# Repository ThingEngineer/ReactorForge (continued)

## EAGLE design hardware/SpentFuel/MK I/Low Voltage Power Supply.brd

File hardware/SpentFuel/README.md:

ReactorForge - SpentFuel
============

SpentFuel is where the older prototypes that have provided a foundation for other models, learning experice and or headaches are stored. Proceed with caution!

Schematic and board designs are in CadSoft EAGLE PCB Design Software.

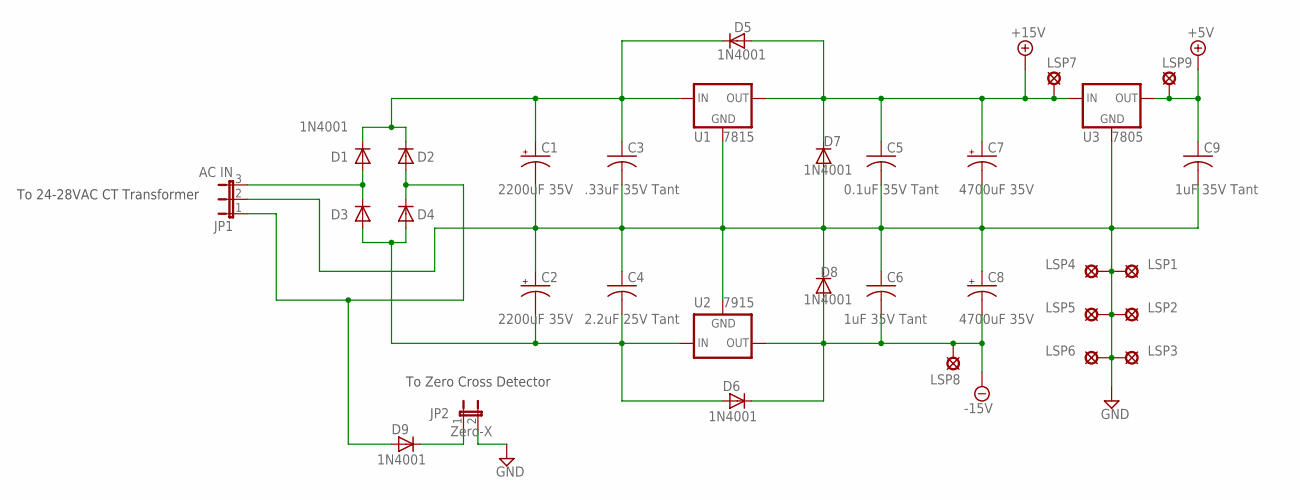
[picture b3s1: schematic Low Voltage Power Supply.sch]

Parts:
C1, C2: 2200uF 35V; E7,5-18
C3: .33uF 35V Tant; C1206
C4: 2.2uF 25V Tant; C1206
C5: 0.1uF 35V Tant; C1206
C6, C9: 1uF 35V Tant; C1206
C7, C8: 4700uF 35V; E7,5-18
D1, D2, D3, D4, D5, D6, D7, D8, D9: 1N4001; DIODE.4-AXIAL
JP1: AC IN; JP2
JP2: Zero-X; JP1
LSP1, LSP2, LSP3, LSP4, LSP5, LSP6, LSP7, LSP8, LSP9: SE14
U1: 7815; 78XXS
U2: 7915; 79XXS
U3: 7805; 78XXS

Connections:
+5V: C9.1, LSP9.MP, U3.OUT
+15V: C5.1, C7.+, D5.A, D7.C, LSP7.MP, U1.OUT, U3.IN
-15V: C6.2, C8.-, D6.C, D8.A, LSP8.MP, U2.OUT
GND: C1.-, C2.+, C3.2, C4.1, C5.2, C6.1, C7.-, C8.+, C9.2, D7.A, D8.C, JP1.2, JP2.2, LSP1.MP, LSP2.MP, LSP3.MP, LSP4.MP, LSP5.MP, LSP6.MP, U1.GND, U2.GND, U3.GND
unnamed: C1.+, C3.1, D1.C, D2.C, D5.C, U1.IN
unnamed: D2.A, D4.C, D9.A, JP1.1
unnamed: D1.A, D3.C, JP1.3
unnamed: C2.-, C4.2, D3.A, D4.A, D6.A, U2.IN
unnamed: D9.C, JP2.1

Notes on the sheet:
To Zero Cross Detector
To 24-28VAC CT Transformer

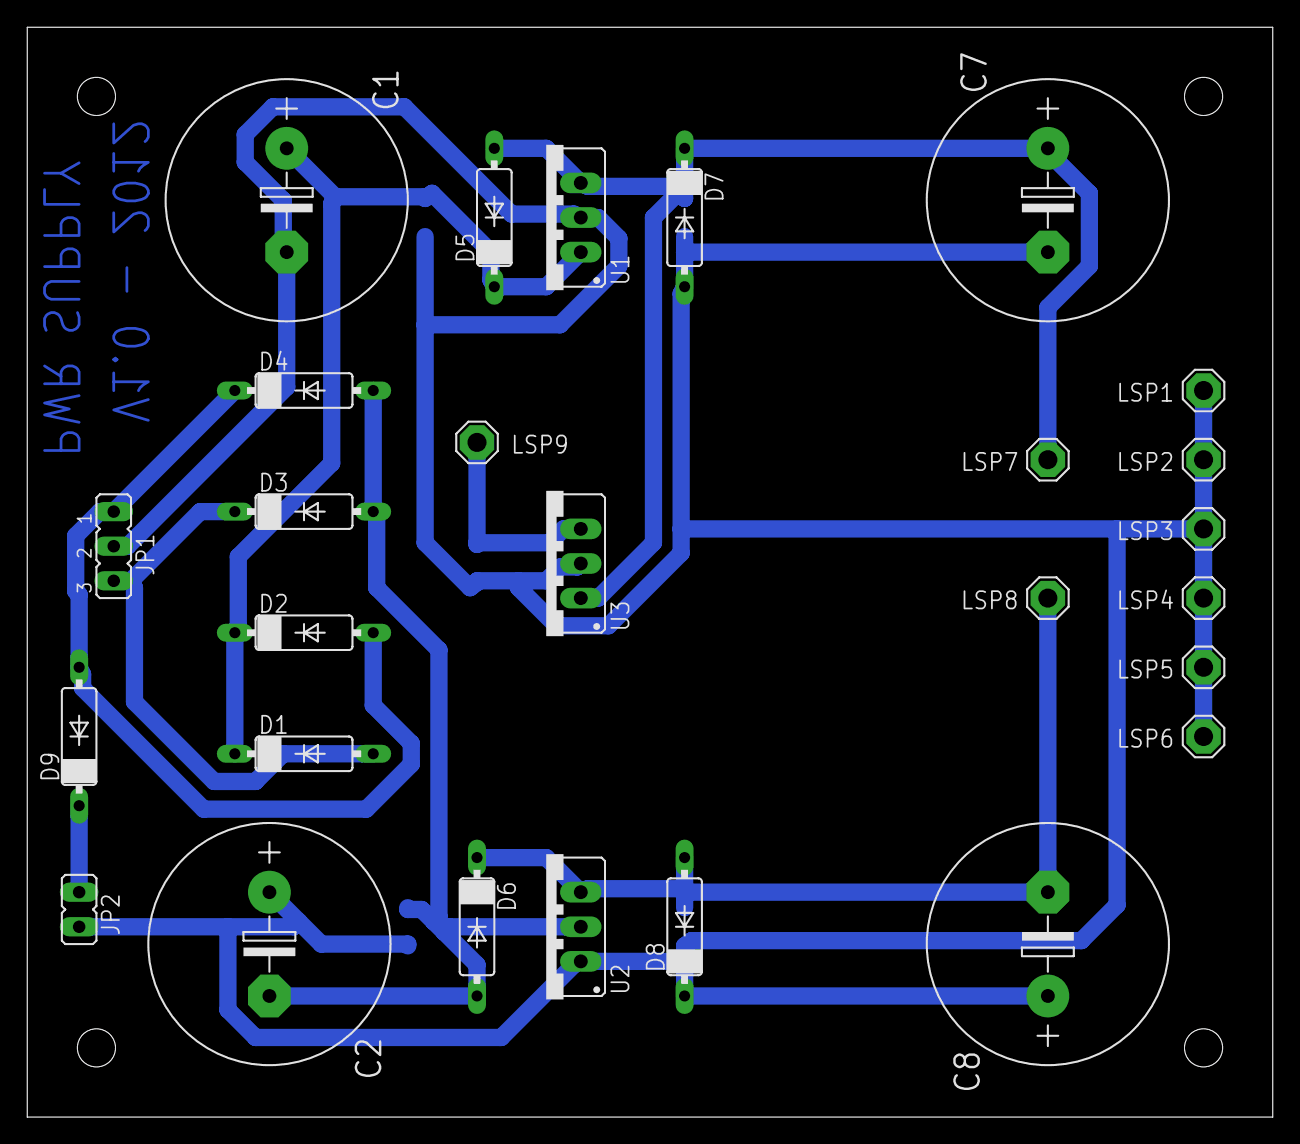
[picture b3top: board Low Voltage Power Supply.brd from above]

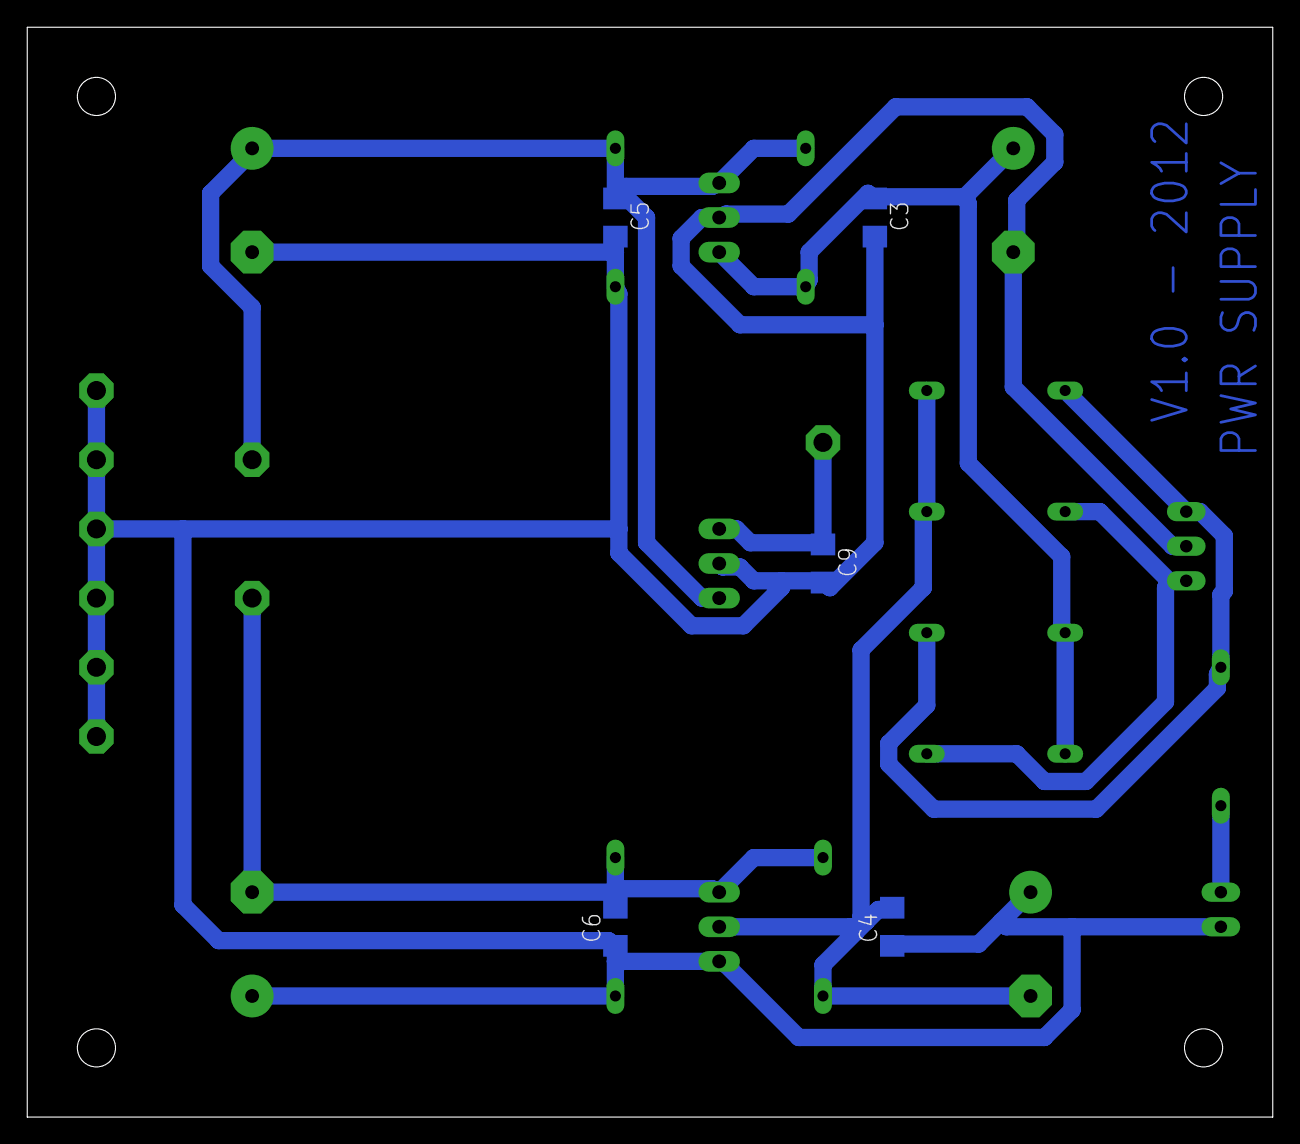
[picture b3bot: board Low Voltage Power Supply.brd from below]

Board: 2 copper layers, 91.4 x 80.0 mm, 32 parts (5 on the bottom side), 9 nets.

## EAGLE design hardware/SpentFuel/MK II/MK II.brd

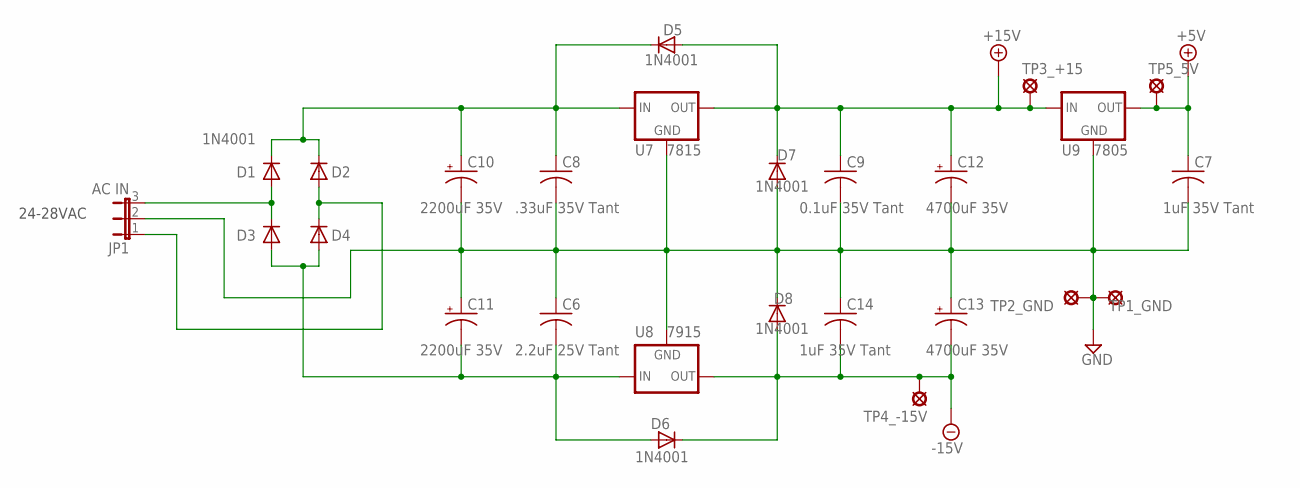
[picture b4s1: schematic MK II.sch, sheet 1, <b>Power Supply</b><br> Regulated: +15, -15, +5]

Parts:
C6: 2.2uF 25V Tant; C1206
C7, C14: 1uF 35V Tant; C1206
C8: .33uF 35V Tant; C1206
C9: 0.1uF 35V Tant; C1206
C10, C11: 2200uF 35V; E7,5-18
C12, C13: 4700uF 35V; E7,5-18
D1, D2, D3, D4, D5, D6, D7, D8: 1N4001; DIODE.4-AXIAL
JP1: AC IN; JP2
TP1_GND, TP2_GND, TP3_+15, TP4_-15V, TP5_5V: SE14
U7: 7815; 78XXS
U8: 7915; 79XXS
U9: 7805; 78XXS

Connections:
+5V: C7.1, TP5_5V.MP, U9.OUT; also elsewhere on the board
+15V: C9.1, C12.+, D5.A, D7.C, TP3_+15.MP, U7.OUT, U9.IN; also elsewhere on the board
-15V: C13.-, C14.2, D6.C, D8.A, TP4_-15V.MP, U8.OUT; also elsewhere on the board
GND: C6.1, C7.2, C8.2, C9.2, C10.-, C11.+, C12.-, C13.+, C14.1, D7.A, D8.C, JP1.2, TP1_GND.MP, TP2_GND.MP, U7.GND, U8.GND, U9.GND; also elsewhere on the board
unnamed: C8.1, C10.+, D1.C, D2.C, D5.C, U7.IN
unnamed: D2.A, D4.C, JP1.1
unnamed: D1.A, D3.C, JP1.3
unnamed: C6.2, C11.-, D3.A, D4.A, D6.A, U8.IN

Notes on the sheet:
24-28VAC

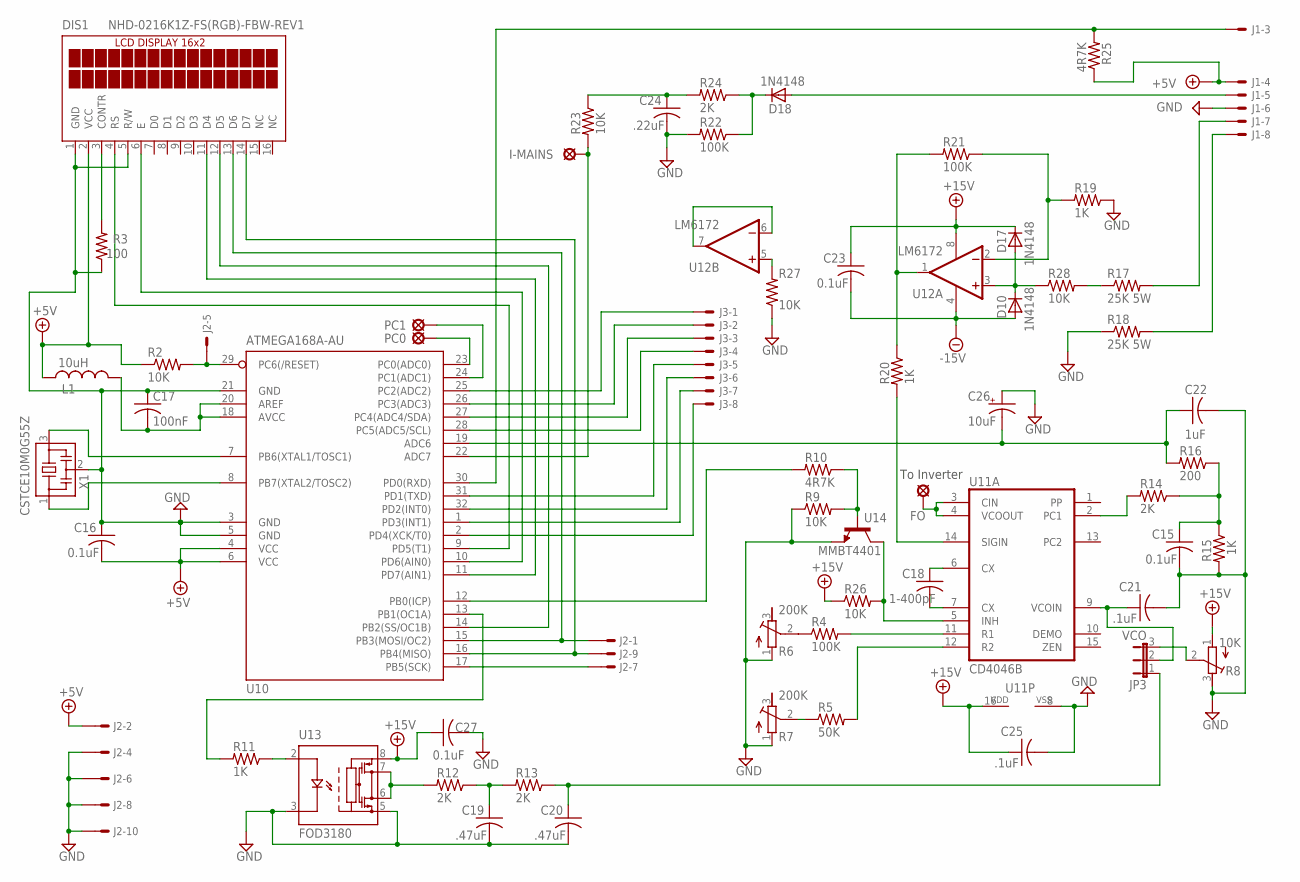
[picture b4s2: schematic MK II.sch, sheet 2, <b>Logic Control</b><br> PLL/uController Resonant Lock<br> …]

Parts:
C15, C16, C23, C27: 0.1uF; C1206
C17: 100nF; C1206
C18: 1-400pF; C1206
C19, C20: .47uF; C1206
C21, C25: .1uF; C1206
C22: 1uF; C1206
C24: .22uF; C1206
C26: 10uF; E2,5-7
D10, D17, D18: 1N4148; SOD-123
DIS1: NHD-0216K1Z-FS(RGB)-FBW-REV1; TUXGR_16X2_R2
FO: SE14
I-MAINS: SE14
J1, J3: 22-23-2081
J2: 057-010-1
JP3: VCO; JP2
L1: 10uH; L2012C
PC0, PC1: SE14
R2, R9, R23, R26, R27, R28: 10K; M1206
R3: 100; M1206
R4, R21, R22: 100K; M1206
R5: 50K; M1206
R6, R7: 200K; RTRIM4G/J
R8: 10K; RTRIM4G/J
R10, R25: 4R7K; M1206
R11, R15, R19, R20: 1K; M1206
R12, R13, R14, R24: 2K; M1206
R16: 200; M1206
R17, R18: 25K 5W; 0617/22
U10: ATMEGA168A-AU; TQFP32-08
U11: CD4046B; SO16
U12: LM6172; SO08
U13: FOD3180; SO08
U14: MMBT4401; SOT23
X1: CSTCE10M0G55Z; 3-SMD

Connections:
1WIRE: J1.3, R25.2, U10.30 (PD0(RXD))
+5V: C16.2, DIS1.2 (VCC), J1.4, J2.2, L1.1, R2.1, R25.1, U10.4 (VCC), U10.6 (VCC); also elsewhere on the board
+15V: C23.1, C25.1, C27.1, D17.C, R8.1 (E), R26.1, U11.16 (VDD), U12.8 (V+), U13.8; also elsewhere on the board
-15V: C23.2, D10.A, U12.4 (V-); also elsewhere on the board
AVCC: C17.2, L1.2, U10.18 (AVCC), U10.20 (AREF)
FO: FO.MP, U11.3 (CIN), U11.4 (VCOOUT); also elsewhere on the board
GND: C15.2, C16.1, C17.1, C19.2, C20.2, C21.2, C22.2, C24.2, C25.2, C26.+, C27.2, DIS1.1 (GND), DIS1.5 (R/W), J1.6, J2.4, J2.6, J2.8, J2.10, R3.1, R6.1 (E), R7.1 (E), R8.3 (A), R9.1, R15.2, R18.1, R19.1, R22.2, R27.1, U10.3 (GND), U10.5 (GND), U10.21 (GND), U11.8 (VSS), U13.3, U13.5, U14.2 (E), X1.2; also elsewhere on the board
GND1: C22.1, C26.-, R16.2, U10.19 (ADC6)
unnamed: D10.C, D17.A, R28.1, U12.3 (+IN)
unnamed: U12.6 (-IN), U12.7 (OUT)
unnamed: D18.A, J1.5
unnamed: U10.8 (PB7(XTAL2/TOSC2)), X1.1
unnamed: U10.7 (PB6(XTAL1/TOSC1)), X1.3
unnamed: J2.5, R2.2, U10.29 (PC6(/RESET))
unnamed: DIS1.3 (CONTR), R3.2
unnamed: R11.1, U13.2
unnamed: DIS1.4 (RS), U10.9 (PD5(T1))
unnamed: DIS1.6 (E), U10.10 (PD6(AIN0))
unnamed: DIS1.11 (D4), U10.11 (PD7(AIN1))
unnamed: DIS1.12 (D5), U10.14 (PB2(SS/OC1B))
unnamed: DIS1.13 (D6), J2.1, U10.15 (PB3(MOSI/OC2))
unnamed: DIS1.14 (D7), J2.9, U10.16 (PB4(MISO))
unnamed: C18.1, U11.6 (CX)
unnamed: C18.2, U11.7 (CX)
unnamed: R4.1, R6.2 (S)
unnamed: R5.1, R7.2 (S)
unnamed: R4.2, U11.11 (R1)
unnamed: R5.2, U11.12 (R2)
unnamed: JP3.3, R8.2 (S)
unnamed: R19.2, R21.1, U12.2 (-IN)
unnamed: R26.2, U11.5 (INH), U14.3 (C)
unnamed: R10.2, U10.12 (PB0(ICP))
unnamed: R11.2, U10.13 (PB1(OC1A))
unnamed: R9.2, R10.1, U14.1 (B)
unnamed: R14.2, U11.2 (PC1)
unnamed: R12.2, U13.6, U13.7
unnamed: C15.1, R14.1, R15.1, R16.1
unnamed: C19.1, R12.1, R13.2
unnamed: C20.1, JP3.1, R13.1
unnamed: C21.1, JP3.2, U11.9 (VCOIN)
unnamed: R27.2, U12.5 (+IN)
unnamed: R20.1, R21.2, U12.1 (OUT)
unnamed: R20.2, U11.14 (SIGIN)
unnamed: R17.1, R28.2
unnamed: J1.8, R18.2
unnamed: C24.1, R23.1, R24.2
unnamed: D18.C, R22.1, R24.1
unnamed: I-MAINS.MP, R23.2, U10.22 (ADC7)
unnamed: J1.7, R17.2
unnamed: J2.7, U10.17 (PB5(SCK))
unnamed: J3.8, U10.2 (PD4(XCK/T0))
unnamed: J3.7, U10.1 (PD3(INT1))
unnamed: J3.6, U10.32 (PD2(INT0))
unnamed: J3.5, U10.31 (PD1(TXD))
unnamed: J3.4, U10.28 (PC5(ADC5/SCL))
unnamed: J3.3, U10.27 (PC4(ADC4/SDA))
unnamed: J3.2, U10.26 (PC3(ADC3))
unnamed: J3.1, U10.25 (PC2(ADC2))
unnamed: PC0.MP, U10.23 (PC0(ADC0))
unnamed: PC1.MP, U10.24 (PC1(ADC1))

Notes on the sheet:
To Inverter

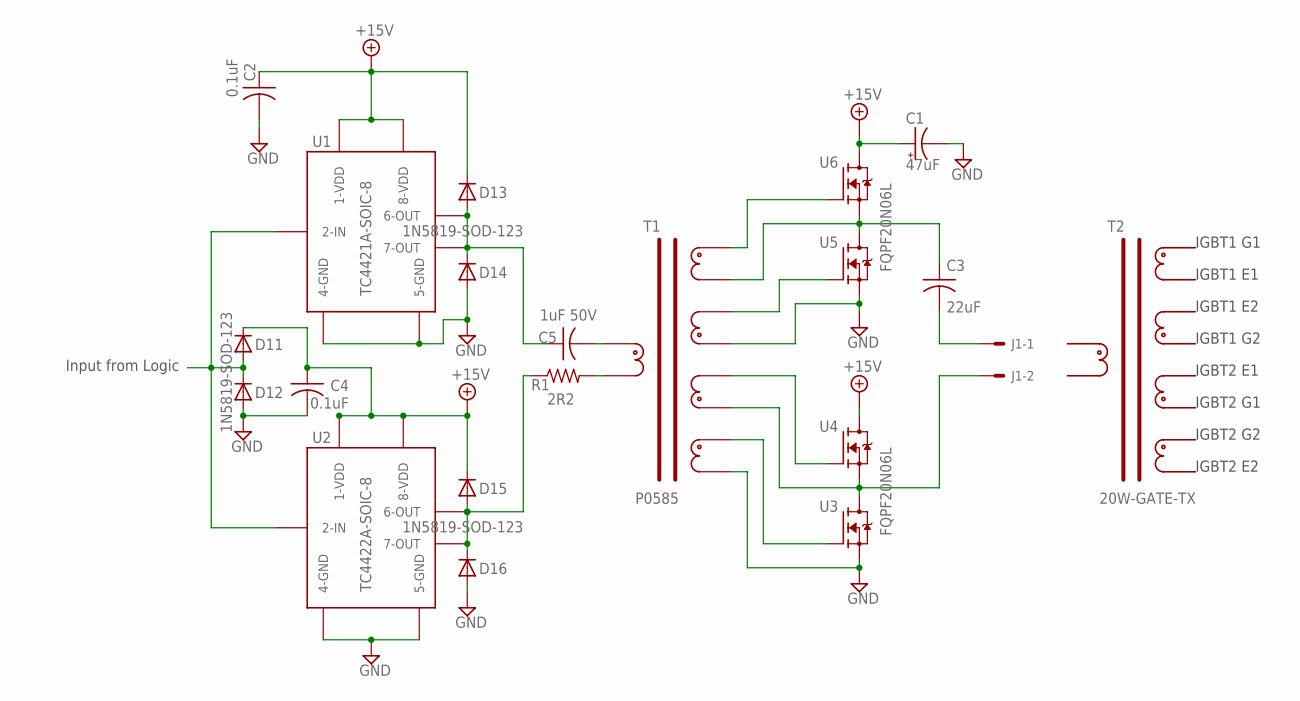
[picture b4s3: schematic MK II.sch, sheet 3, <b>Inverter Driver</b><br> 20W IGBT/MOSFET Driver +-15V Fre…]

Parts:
C1: 47uF; E2,5-7
C2, C4: 0.1uF; C1206
C3: 22uF; C1206
C5: 1uF 50V; C1206
D11, D12, D13, D14, D15, D16: 1N5819-SOD-123; SOD-123
J1: 22-23-2081
R1: 2R2; 0207/10
T1: P0585
U1: TC4421A-SOIC-8; SOIC-8
U2: TC4422A-SOIC-8; SOIC-8
U3, U4, U5, U6: FQPF20N06L; TO-220-V

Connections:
+15V: C1.+, C2.1, C4.1, D11.C, D13.C, D15.C, U1.P$1 (1-VDD), U1.P$8 (8-VDD), U2.P$1 (1-VDD), U2.P$8 (8-VDD), U4.2 (D), U6.2 (D); also elsewhere on the board
FO: D11.A, D12.C, U1.P$2 (2-IN), U2.P$2 (2-IN); also elsewhere on the board
GND: C1.-, C2.2, C4.2, D12.A, D14.A, D16.A, T1.P$4, T1.P$6, U1.P$4 (4-GND), U1.P$5 (5-GND), U2.P$4 (4-GND), U2.P$5 (5-GND), U3.3 (S), U5.3 (S); also elsewhere on the board
unnamed: J1.2, T1.P$9, U3.2 (D), U4.3 (S)
unnamed: C5.1, D13.A, D14.C, U1.P$6 (6-OUT), U1.P$7 (7-OUT)
unnamed: C5.2, T1.P$1
unnamed: R1.2, T1.P$10
unnamed: D15.A, D16.C, R1.1, U2.P$6 (6-OUT), U2.P$7 (7-OUT)
unnamed: C3.1, T1.P$3, U5.2 (D), U6.3 (S)
unnamed: T1.P$2, U6.1 (G)
unnamed: T1.P$5, U5.1 (G)
unnamed: T1.P$8, U4.1 (G)
unnamed: T1.P$7, U3.1 (G)
unnamed: C3.2, J1.1

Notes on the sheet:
Input from Logic
IGBT1 G1
IGBT1 E1
IGBT1 E2
IGBT1 G2
IGBT2 G1
IGBT2 E1
IGBT2 E2
IGBT2 G2

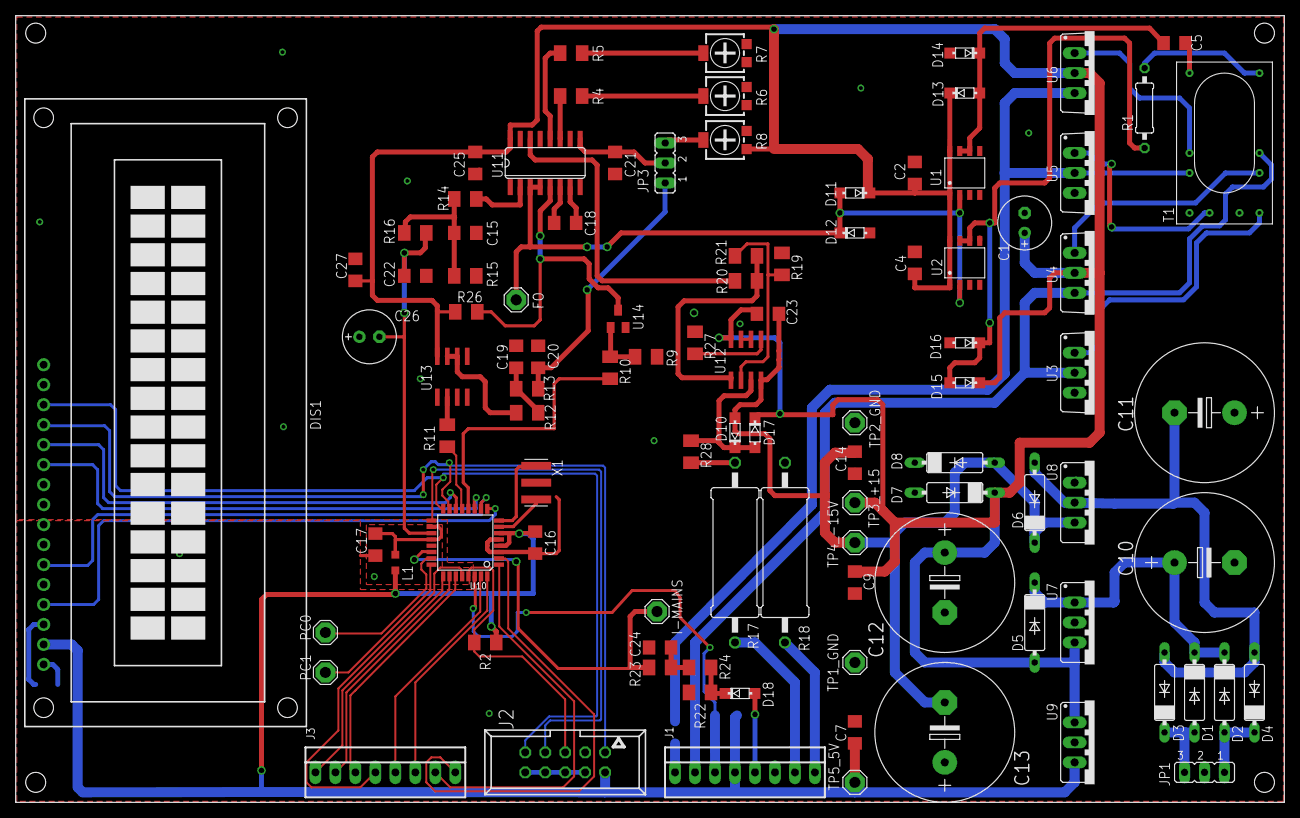
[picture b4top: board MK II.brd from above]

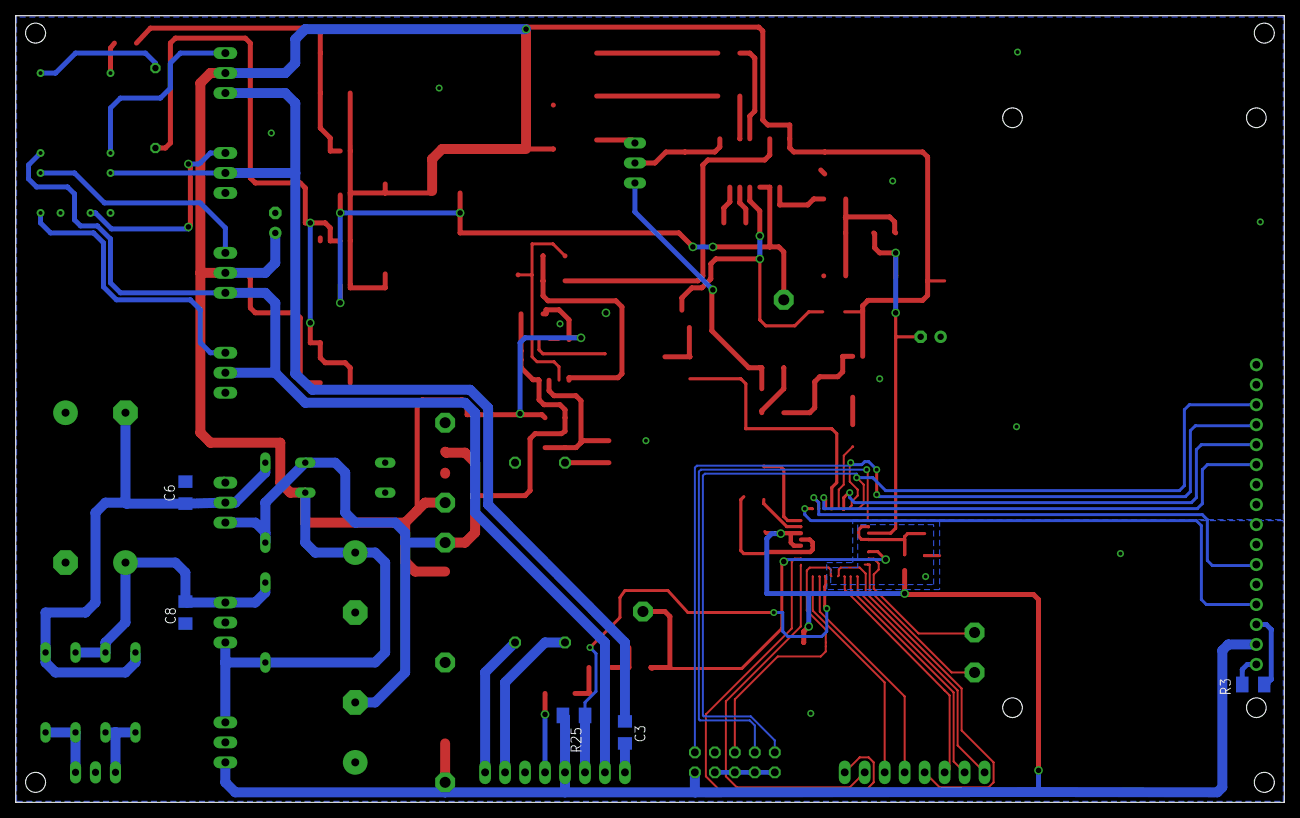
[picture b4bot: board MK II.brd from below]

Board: 2 copper layers, 161.3 x 100.0 mm, 104 parts (5 on the bottom side), 75 nets.

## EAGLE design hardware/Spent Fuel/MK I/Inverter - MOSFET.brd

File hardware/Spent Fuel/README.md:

ReactorForge - SpentFuel
============

SpentFuel is the code name for older prototypes that have provided a foundation for other models, learning experice and or headaches. They will likely remain here in storage. Proceed with caution!

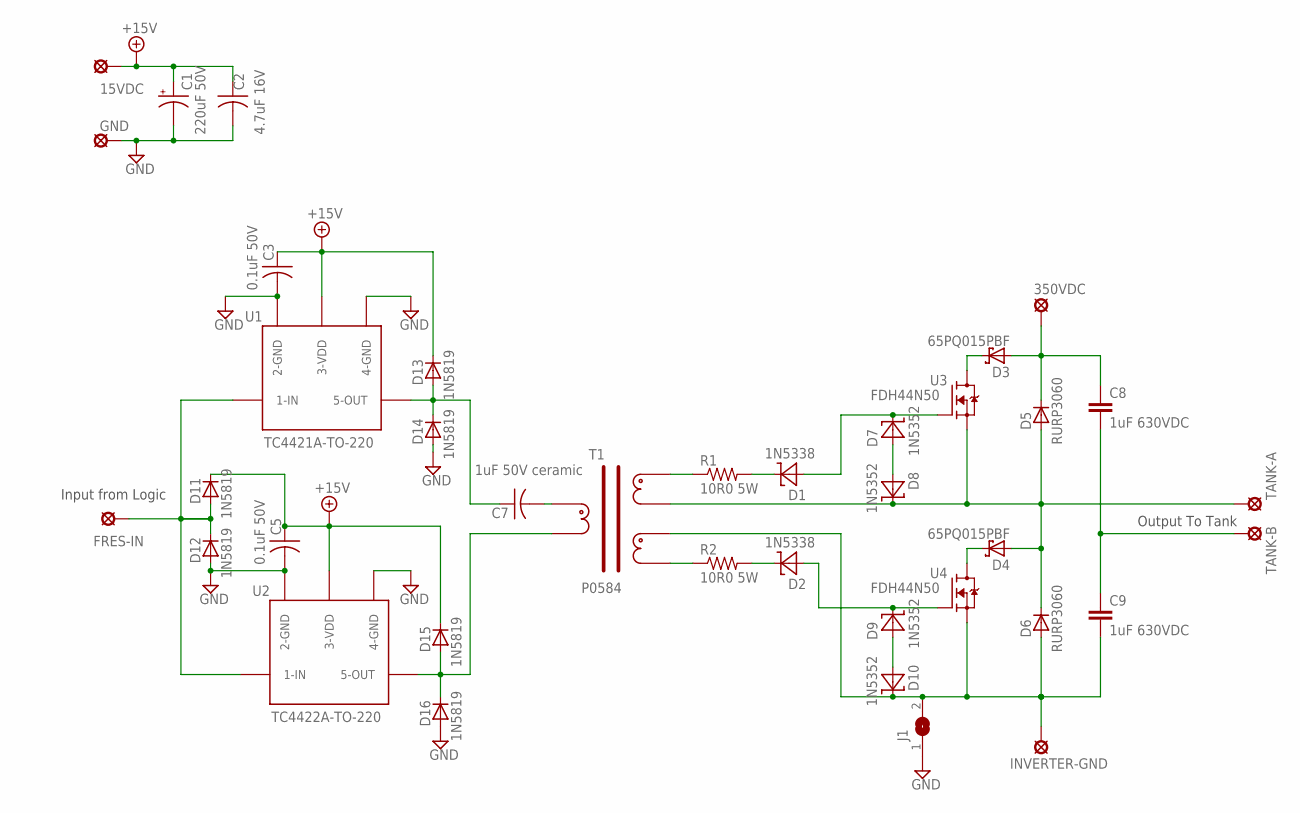
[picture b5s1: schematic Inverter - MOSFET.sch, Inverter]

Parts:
15VDC, 350VDC: SE14
C1: 220uF 50V; E5-10,5
C2: 4.7uF 16V; C1206
C3, C5: 0.1uF 50V; C1206
C7: 1uF 50V ceramic; C1206
C8, C9: 1uF 630VDC; CAPACITOR2.2-AXIAL
D1, D2: 1N5338; DIODE.4-AXIAL
D3, D4: 65PQ015PBF; TO-247AC-V
D5, D6: RURP3060; TO-220CA2-V
D7, D8, D9, D10: 1N5352; DIODE.4-AXIAL
D11, D12, D13, D14, D15, D16: 1N5819; DIODE.4-AXIAL
FRES-IN: SE14
GND: SE14
INVERTER-GND: SE14
J1: SJW
R1, R2: 10R0 5W; P0817/22
T1: P0584
TANK-A: SE14
TANK-B: SE14
U1: TC4421A-TO-220; TO-220-8TAB-H
U2: TC4422A-TO-220; TO-220-8TAB-H
U3, U4: FDH44N50; TO-247-V

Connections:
350VDC: 350VDC.MP, C8.P$1 (1), D3.1 (A), D3.3 (A), D5.C
+15V: 15VDC.MP, C1.+, C2.1, C3.1, C5.1, D11.C, D13.C, D15.C, U1.3 (3-VDD), U1.TAB (3-VDD), U2.3 (3-VDD), U2.TAB (3-VDD)
GND1: C1.-, C2.2, C3.2, C5.2, D12.A, D14.A, D16.A, GND.MP, J1.1, U1.2 (2-GND), U1.4 (4-GND), U2.2 (2-GND), U2.4 (4-GND)
INVERTER-GND: C9.P$2 (2), D6.A, D10.C, INVERTER-GND.MP, J1.2, T1.P$8, U4.3 (S)
unnamed: D11.A, D12.C, FRES-IN.MP, U1.1 (1-IN), U2.1 (1-IN)
unnamed: C7.1, D13.A, D14.C, U1.5 (5-OUT)
unnamed: C7.2, T1.P$1
unnamed: R1.1, T1.P$3
unnamed: D15.A, D16.C, T1.P$10, U2.5 (5-OUT)
unnamed: R2.1, T1.P$7
unnamed: D1.C, R1.2
unnamed: D2.C, R2.2
unnamed: D3.2 (C), U3.2 (D)
unnamed: D4.2 (C), U4.2 (D)
unnamed: D9.A, D10.A
unnamed: D7.A, D8.A
TANK-A: D4.1 (A), D4.3 (A), D5.A, D6.C, D8.C, T1.P$4, TANK-A.MP, U3.3 (S)
TANK-B: C8.P$2 (2), C9.P$1 (1), TANK-B.MP
U3-GATE: D1.A, D7.C, U3.1 (G)
U4-GATE: D2.A, D9.C, U4.1 (G)

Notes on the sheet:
Output To Tank
Input from Logic

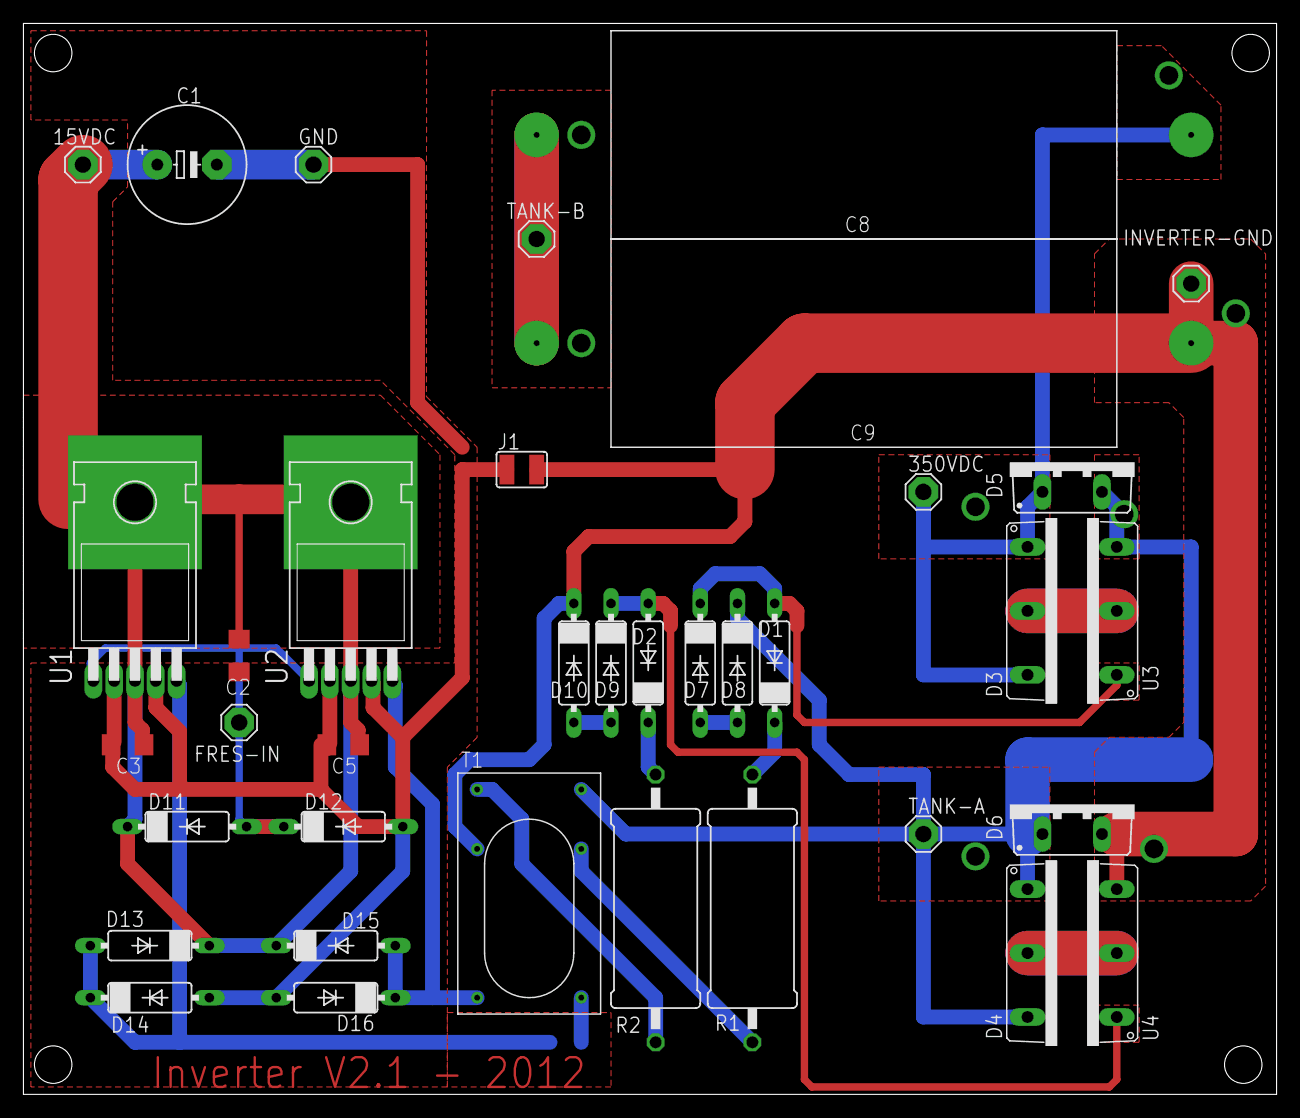
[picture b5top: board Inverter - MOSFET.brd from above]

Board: 2 copper layers, 107.0 x 91.4 mm, 38 parts (1 on the bottom side), 20 nets.

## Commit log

2014-06-07 add root .getignore
2014-06-07 add hardware gitignore
2014-06-07 add doc folder
2014-06-07 add photo of beta assembly
2014-06-07 add description and photo
2014-06-07 add photo caption
2014-06-07 wording change
2014-06-07 add hardware model readme files
2014-06-07 add Kvar beer analogy image
2014-06-07 changed image format
2014-06-08 added project description
2014-06-08 project description update
2014-06-08 add readme
2014-06-11 update assembly photo
2014-06-11 update hardware ignore file
2014-06-11 Add MKI schematic and board files
2014-06-11 Add MKII schematic and board files
2014-06-11 Update LICENSE
2014-06-11 removed space from directory name
2014-06-11 add firmware ignore file
2014-06-11 update ignore file
2014-06-11 add MKI code
2014-06-11 add MKII code
2014-06-11 add criticalmass video screen shot
2014-06-14 added MKII control upgrade board image
2014-06-14 initial commit for ReactorGraph processing sketch
2014-06-14 add processing before/after ss
2014-06-14 update config
2014-06-14 remove .JPG
2014-06-14 add .jpg
2014-06-14 update header
2014-06-14 add logo transparent
2014-06-15 add core front and back photos
2014-06-15 resized images and changed jpg to png
2014-06-15 update image link
2014-06-15 add MKII upgrade readme
2014-06-15 update read me
2014-06-15 removed ss
2014-06-15 add Hybrid Driver files
2014-06-15 typo
2014-06-16 add source folder & files
2014-06-16 add hybrid driver connections
2014-06-16 add connections image
2014-06-16 removed transparency
2014-06-16 resized
2014-06-16 remove hardware folders for future models
2014-06-16 update description
2014-06-16 moved documentation to wiki
2014-06-16 update documentation link
2014-06-16 add safety notice
2014-06-16 update safety notice header
2014-06-16 change project status sentence
2014-06-16 add item to safety notice
2014-06-16 change logo color
2014-06-16 added more MKII to MKIII control upgrade photos, updated readme
2014-06-16 update images and readme
2014-06-16 fix whitespace
2014-06-16 bold headers, fix name
2014-06-16 add and update driver images
2014-06-16 Update README.md
    just a typo I found while reading enthusiastically
2014-06-16 move and update images (added legend)
2014-06-16 moved image, updated link and title
2014-06-16 updated safety notice and typos
2014-06-18 added PPE to safety notice
2015-02-06 Added parts list/BOM
2015-08-22 Updated Readme/Safety Notice
2017-11-10 Update readme
    Added Patreon link and changed safety notice
2017-11-14 Updated readme
    Changed Patreon message
2017-11-14 Update readme
    Typo
2017-11-16 Fixed image names on MK III upgrade
2017-11-16 Changed MK II Upgrade folder name
    MK III = MK II Upgrade
2017-11-16 CriticalMass ReactorForge Core
    Initial Github commit for this schematic and board file
2017-11-16 Added .OLD to file names to prevent Github from saying this repository is of the VisualBasic language
2017-11-19 Update .gitignore
    Removed old Bascom files and added Atmel Studio Debug/ directory.
2017-11-20 Update readme
    tweak description
2017-11-20 Update readme
    Added blog link
2017-11-27 Update readme
    http to https
2017-12-07 Create Blog Update Notification
2017-12-14 Initial commit for CriticalMass Firmware PlatformIO Project
2017-12-15 not using TravisCI
2017-12-15 setup environment
2017-12-15 test code
2017-12-15 auto re-generated
2017-12-15 change variable type
2017-12-15 add f_cpu to ini
2017-12-15 add fuses to ini
2017-12-15 Custom AT90PWM316 board manifest for platformio
2017-12-15 moved platformio board manifest to project scope
2017-12-15 removed f_cpu from board manifest
2017-12-15 changed boad name in board manifest
2017-12-15 vendor name tweak in board manifest
2017-12-15 corrected flash size in board manifest
2017-12-15 changed fuse bytes in board manifest to chip defaults
2017-12-15 added custom script in platformio.ini to set fuse bytes
2017-12-15 revert old BASCOM basic firmware files back to original file names
2017-12-15 custom fuses commented out while testing platform
2017-12-16 changed programmer
2017-12-16 added development environment description
2017-12-16 removed f_cpu from main, handled in platformio.ini
2017-12-16 travis ci test1
2017-12-16 remove travis ci test1
2017-12-16 removed test main.cpp
2017-12-17 removed .platformio/boards, using project level board manifest
2017-12-17 updated project level board manifest, removed lock fuse and corrected default lfuse
2017-12-17 added another fuse calculator
2017-12-17 removed extra_script, did not work for programing fuses, using upload_flags
2017-12-17 changed f_cpu variable type
2017-12-17 removed duplicate
2017-12-17 avrdude flag typo
2017-12-17 moved fuse flags to platformio.ini
2017-12-17 refined fuse comments
2017-12-17 added chip erase command because platformio is doing a -D, this causes any changes to the program to not verify, wth
2017-12-21 added fuse bit to preserve EEPROM through chip erase
2017-12-21 added modified dependencies
2017-12-21 added remaining header file
2017-12-22 fixed main header types
2017-12-22 main code commit, pre-cleanup
2017-12-22 added build flags, need to test
2017-12-22 updated main.c documentation
2017-12-22 add TODO.txt
2017-12-22 update TODO
2017-12-22 moved to TODO.txt
2017-12-22 elaboriate on set_frequency description
2017-12-23 format correction on fuse comments
2017-12-23 added f_cpu back to the board manafest so platformIO shows cpu speed correctly in the Board Explorer
2017-12-24 added F macro
2017-12-24 removed local board manafest, support merged with platform-atmelavr 1.8.1
2017-12-27 TODO format
2017-12-27 debuging serial device selection
2017-12-27 activate contactor on startup
2017-12-27 move ideas to IDEAS.txt
2017-12-27 added licence link
2017-12-28 removed beeper test code
2017-12-28 removed Start/Stop switch & indicator light test code
2017-12-28 removed button press adc value readout test code
2017-12-28 removed contactor/pump switch test code
2017-12-28 removed additional button testing code
2017-12-28 removed temperature sensor test code
2017-12-28 removed zero cross detection test code
2017-12-28 removed additional beeper test code - good interupt test code!
2017-12-28 tweaked startup menu
2017-12-28 comment main() startup code
2017-12-28 removed Multiplexed buttons pull up, using external hardware pullup
2017-12-28 cleaned up setup() comments
2017-12-28 added missing setup() comments
2017-12-28 added alias for encoder output B
2017-12-28 added IGBT_FAULT alias
2017-12-28 TODO addition
2017-12-28 removed internal encoder pull ups, they have external pull ups
2017-12-28 removed start/stop switch pull up, it has an external pull ups
2017-12-28 updated incr_freq function, documentation, and added TODO
2017-12-28 updated decr_freq function and documentation
2017-12-28 incr & decr frequency comment tweaks
2017-12-28 incr_freq TODO notes
2017-12-28 IGBT_FAULT_PIN has a pull up on the driver board, leave soft pull up for better noise immunity
2017-12-31 removed old board version copy
2017-12-31 reduced board width to 2 inches, added decoupling cap on 5V supply, updated documentation and library components
2017-12-31 updated BOM
2017-12-31 added OSH logo, tweaked silkscreen
2018-01-02 add library
2018-01-05 added design PDF
2018-01-10 moved OSH logo down, added board renderings
2018-01-11 convert OSH logo text to vector
2018-01-11 silk screen placment tweaks
2018-01-11 increase G1 & G2 net width to 0.032
2018-01-11 more small silk screen placment tweaks
2018-01-12 added BOM with details, links, and pricing
2018-01-13 added 0 ohm jumper
2018-04-11 Update blog notice and gitignore
2018-09-26 add BOM, Schematic, and Layout
2018-09-26 update file names
2018-09-26 update filename
2018-09-26 update filenames
